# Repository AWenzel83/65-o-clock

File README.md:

# 65-o-clock
6502 based clock heavily inspired by Ben Eaters 6502-Breadboard-Computer (https://eater.net/6502)

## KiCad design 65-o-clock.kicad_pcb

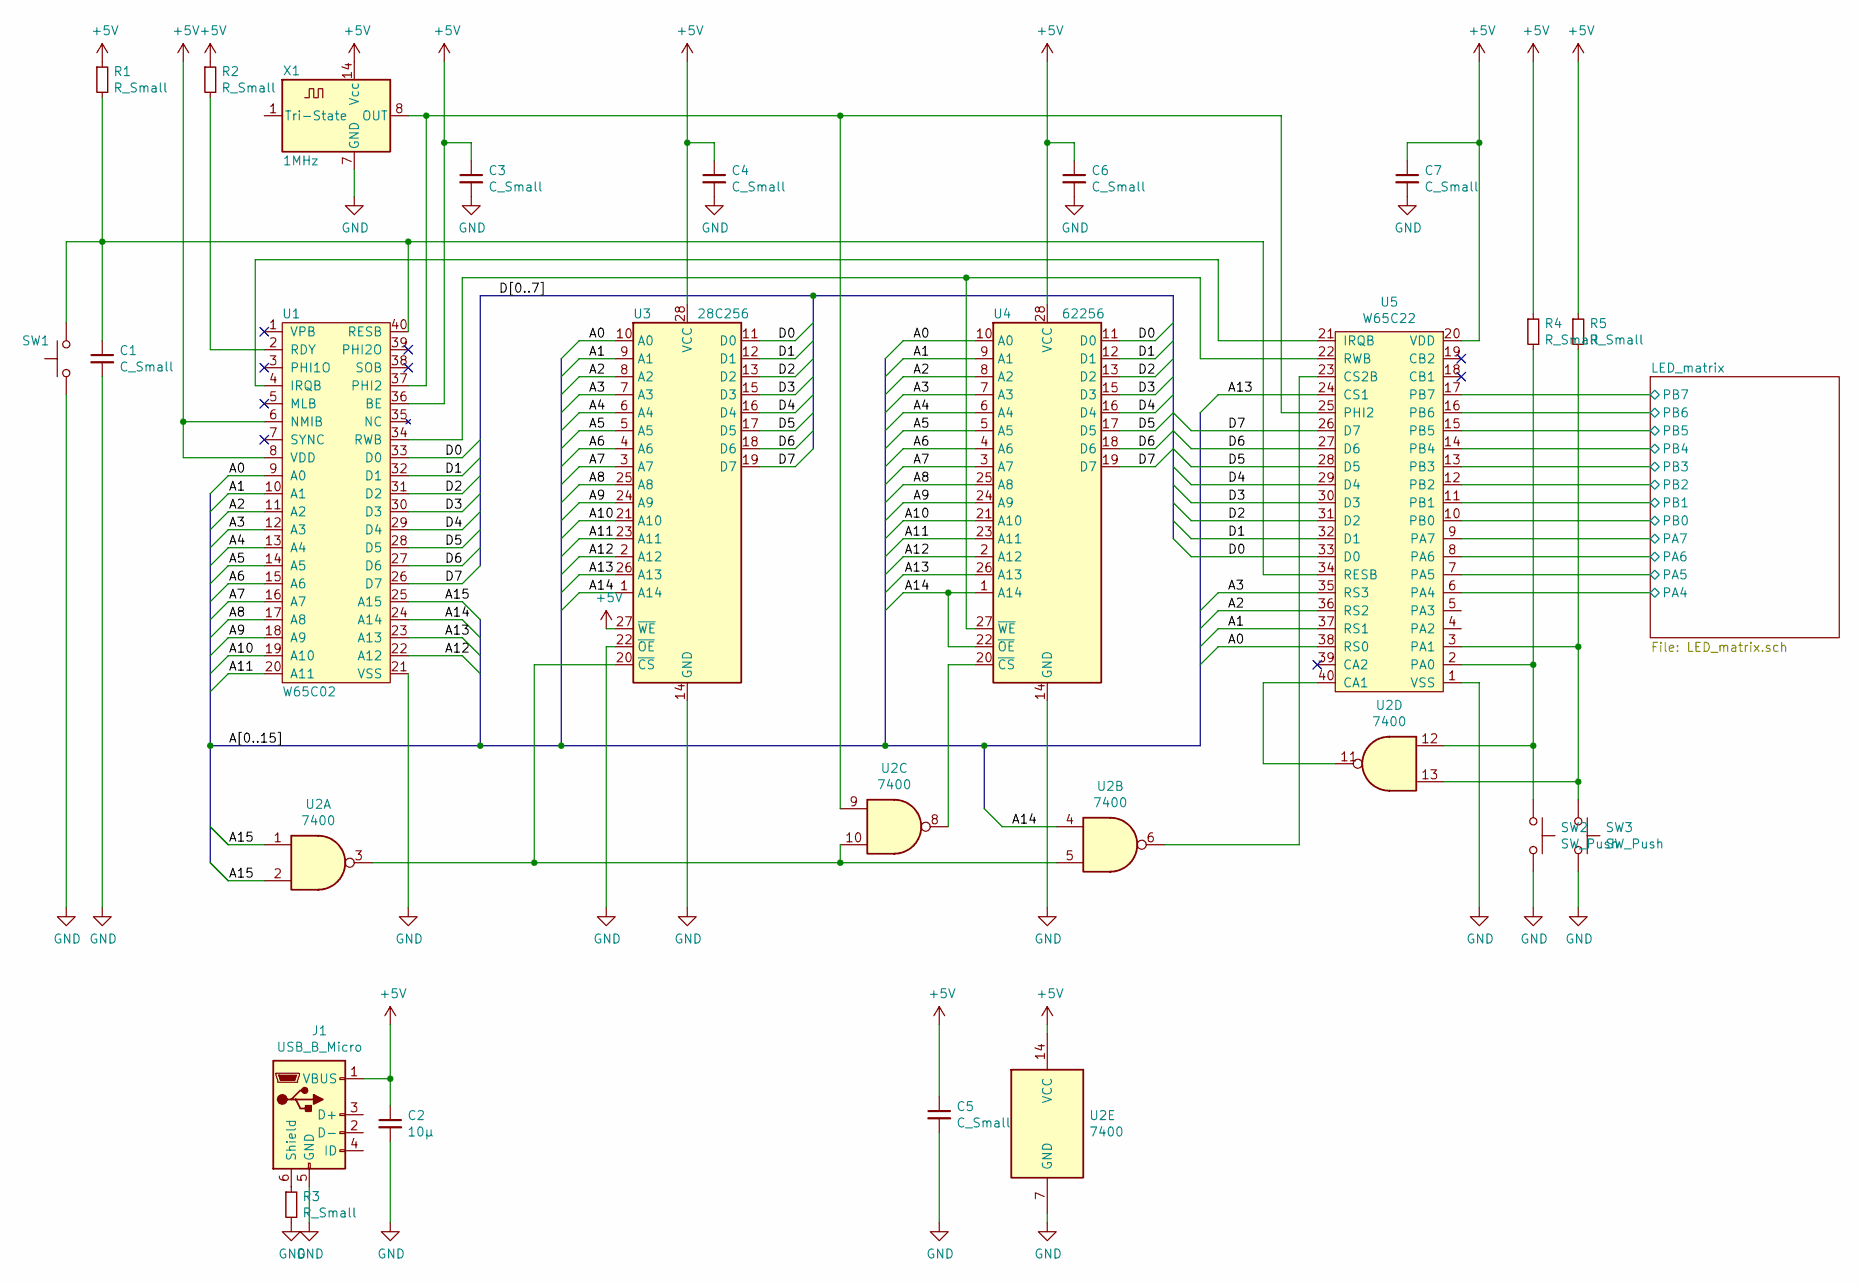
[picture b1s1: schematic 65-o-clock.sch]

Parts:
C1, C3, C4, C5, C6, C7: C_Small; C_0603_1608Metric_Pad1.05x0.95mm_HandSolder
C2: 10µ; C_1206_3216Metric_Pad1.42x1.75mm_HandSolder
J1: USB_B_Micro; USB_Micro-B_Molex-105017-0001
R1, R2, R3, R4, R5: R_Small; R_0603_1608Metric_Pad1.05x0.95mm_HandSolder
SW1, SW2, SW3: SW_Push; SW_Tactile_SPST_Angled_PTS645Vx39-2LFS
U1: W65C02; DIP-40_W15.24mm_Socket_LongPads
U2: 7400; DIP-14_W7.62mm_Socket_LongPads
U3: 28C256; DIP-28_W15.24mm_Socket_LongPads
U4: 62256; DIP-28_W15.24mm_Socket_LongPads
U5: W65C22; DIP-40_W15.24mm_Socket_LongPads
X1: 1MHz; Oscillator_DIP-14

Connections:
+5V: C2.1, C3.1, C4.1, C5.1, C6.1, C7.1, J1.1 (VBUS), R1.1, R2.1, R4.1, R5.1, U1.6 (NMIB), U1.8 (VDD), U1.36 (BE), U2.14 (VCC), U3.27 (~WE), U3.28 (VCC), U4.28 (VCC), U5.20 (VDD), X1.14 (Vcc); also elsewhere on the board
/A0: U1.9 (A0), U3.10 (A0), U4.10 (A0), U5.38 (RS0)
/A1: U1.10 (A1), U3.9 (A1), U4.9 (A1), U5.37 (RS1)
/A2: U1.11 (A2), U3.8 (A2), U4.8 (A2), U5.36 (RS2)
/A3: U1.12 (A3), U3.7 (A3), U4.7 (A3), U5.35 (RS3)
/A4: U1.13 (A4), U3.6 (A4), U4.6 (A4)
/A5: U1.14 (A5), U3.5 (A5), U4.5 (A5)
/A6: U1.15 (A6), U3.4 (A6), U4.4 (A6)
/A7: U1.16 (A7), U3.3 (A7), U4.3 (A7)
/A8: U1.17 (A8), U3.25 (A8), U4.25 (A8)
/A9: U1.18 (A9), U3.24 (A9), U4.24 (A9)
/A10: U1.19 (A10), U3.21 (A10), U4.21 (A10)
/A11: U1.20 (A11), U3.23 (A11), U4.23 (A11)
/A12: U1.22 (A12), U3.2 (A12), U4.2 (A12)
/A13: U1.23 (A13), U3.26 (A13), U4.26 (A13), U5.24 (CS1)
/A14: U1.24 (A14), U2.4, U3.1 (A14), U4.1 (A14), U4.22 (~OE)
/A15: U1.25 (A15), U2.1, U2.2
/D0: U1.33 (D0), U3.11 (D0), U4.11 (D0), U5.33 (D0)
/D1: U1.32 (D1), U3.12 (D1), U4.12 (D1), U5.32 (D1)
/D2: U1.31 (D2), U3.13 (D2), U4.13 (D2), U5.31 (D2)
/D3: U1.30 (D3), U3.15 (D3), U4.15 (D3), U5.30 (D3)
/D4: U1.29 (D4), U3.16 (D4), U4.16 (D4), U5.29 (D4)
/D5: U1.28 (D5), U3.17 (D5), U4.17 (D5), U5.28 (D5)
/D6: U1.27 (D6), U3.18 (D6), U4.18 (D6), U5.27 (D6)
/D7: U1.26 (D7), U3.19 (D7), U4.19 (D7), U5.26 (D7)
/LED_matrix/PA4: U5.6 (PA4); also elsewhere on the board
/LED_matrix/PA5: U5.7 (PA5); also elsewhere on the board
/LED_matrix/PA6: U5.8 (PA6); also elsewhere on the board
/LED_matrix/PA7: U5.9 (PA7); also elsewhere on the board
/LED_matrix/PB0: U5.10 (PB0); also elsewhere on the board
/LED_matrix/PB1: U5.11 (PB1); also elsewhere on the board
/LED_matrix/PB2: U5.12 (PB2); also elsewhere on the board
/LED_matrix/PB3: U5.13 (PB3); also elsewhere on the board
/LED_matrix/PB4: U5.14 (PB4); also elsewhere on the board
/LED_matrix/PB5: U5.15 (PB5); also elsewhere on the board
/LED_matrix/PB6: U5.16 (PB6); also elsewhere on the board
/LED_matrix/PB7: U5.17 (PB7); also elsewhere on the board
GND: C1.2, C2.2, C3.2, C4.2, C5.2, C6.2, C7.2, J1.5 (GND), R3.2, SW1.1, SW2.2, SW3.2, U1.21 (VSS), U2.7 (GND), U3.14 (GND), U3.22 (~OE), U4.14 (GND), U5.1 (VSS), X1.7 (GND); also elsewhere on the board
unnamed: C1.1, R1.2, SW1.2, U1.40 (RESB), U5.34 (RESB)
unnamed: J1.6 (Shield), R3.1
unnamed: R2.2, U1.2 (RDY)
unnamed: R4.2, SW2.1, U2.12, U5.2 (PA0)
unnamed: R5.2, SW3.1, U2.13, U5.3 (PA1)
unnamed: U1.4 (IRQB), U5.21 (IRQB)
unnamed: U1.34 (RWB), U4.27 (~WE), U5.22 (RWB)
unnamed: U1.37 (PHI2), U2.9, U5.25 (PHI2), X1.8 (OUT)
unnamed: U2.6, U5.23 (CS2B)
unnamed: U2.8, U4.20 (~CS)
unnamed: U2.3, U2.5, U2.10, U3.20 (~CS)
unnamed: U2.11, U5.40 (CA1)

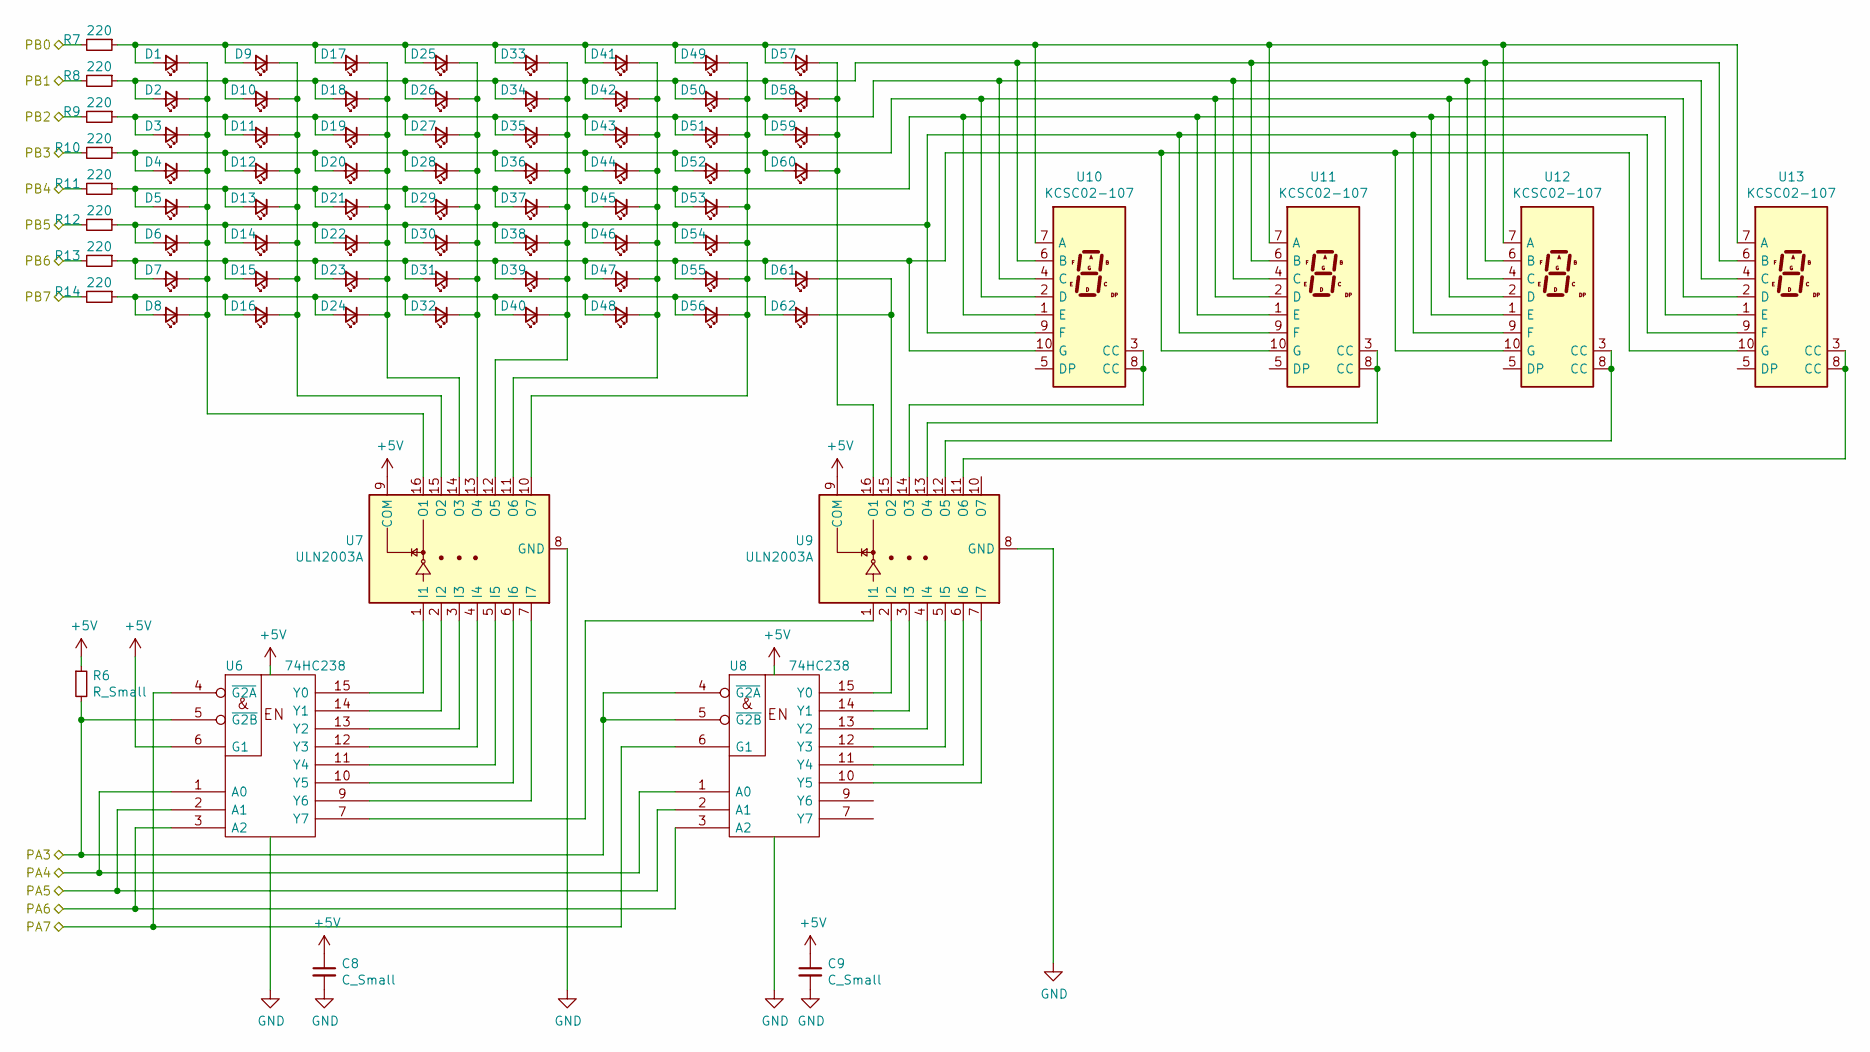
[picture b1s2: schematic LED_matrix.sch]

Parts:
C8, C9: C_Small; C_0603_1608Metric_Pad1.05x0.95mm_HandSolder
D1, D2, D3, D4, D5, D6, D7, D8, D9, D10, D11, D12, D13, D14, D15, D16, D17, D18, D19, D20, D21, D22, D23, D24, D25, D26, D27, D28, D29, D30, D31, D32, D33, D34, D35, D36, D37, D38, D39, D40, D41, D42, D43, D44, D45, D46, D47, D48, D49, D50, D51, D52, D53, D54, D55, D56, D57, D58, D59, D60, D61, D62: LED_Small; LED_D5.0mm
R6: R_Small; R_0603_1608Metric_Pad1.05x0.95mm_HandSolder
R7, R8, R9, R10, R11, R12, R13, R14: 220; R_0603_1608Metric_Pad1.05x0.95mm_HandSolder
U6, U8: 74HC238; DIP-16_W7.62mm_Socket_LongPads
U7, U9: ULN2003A; DIP-16_W7.62mm_Socket_LongPads
U10, U11, U12, U13: KCSC02-107; 7SegmentLED_LTS6760_LTS6780

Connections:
+5V: C8.1, C9.1, R6.1, U6.6 (G1), U6.16 (VCC), U7.9 (COM), U8.16 (VCC), U9.9 (COM); also elsewhere on the board
/LED_matrix/PA3: R6.2, U6.5 (~G2B), U8.4 (~G2A), U8.5 (~G2B)
/LED_matrix/PA4: U6.1 (A0), U8.1 (A0); also elsewhere on the board
/LED_matrix/PA5: U6.2 (A1), U8.2 (A1); also elsewhere on the board
/LED_matrix/PA6: U6.3 (A2), U8.3 (A2); also elsewhere on the board
/LED_matrix/PA7: U6.4 (~G2A), U8.6 (G1); also elsewhere on the board
/LED_matrix/PB0: R7.2; also elsewhere on the board
/LED_matrix/PB1: R8.2; also elsewhere on the board
/LED_matrix/PB2: R9.2; also elsewhere on the board
/LED_matrix/PB3: R10.2; also elsewhere on the board
/LED_matrix/PB4: R11.2; also elsewhere on the board
/LED_matrix/PB5: R12.2; also elsewhere on the board
/LED_matrix/PB6: R13.2; also elsewhere on the board
/LED_matrix/PB7: R14.2; also elsewhere on the board
GND: C8.2, C9.2, U6.8 (GND), U7.8 (GND), U8.8 (GND), U9.8 (GND); also elsewhere on the board
unnamed: D1.1 (K), D2.1 (K), D3.1 (K), D4.1 (K), D5.1 (K), D6.1 (K), D7.1 (K), D8.1 (K), U7.16 (O1)
unnamed: D1.2 (A), D9.2 (A), D17.2 (A), D25.2 (A), D33.2 (A), D41.2 (A), D49.2 (A), D57.2 (A), R7.1, U10.7 (A), U11.7 (A), U12.7 (A), U13.7 (A)
unnamed: D9.1 (K), D10.1 (K), D11.1 (K), D12.1 (K), D13.1 (K), D14.1 (K), D15.1 (K), D16.1 (K), U7.15 (O2)
unnamed: D2.2 (A), D10.2 (A), D18.2 (A), D26.2 (A), D34.2 (A), D42.2 (A), D50.2 (A), D58.2 (A), R8.1, U10.6 (B), U11.6 (B), U12.6 (B), U13.6 (B)
unnamed: D3.2 (A), D11.2 (A), D19.2 (A), D27.2 (A), D35.2 (A), D43.2 (A), D51.2 (A), D59.2 (A), R9.1, U10.4 (C), U11.4 (C), U12.4 (C), U13.4 (C)
unnamed: D4.2 (A), D12.2 (A), D20.2 (A), D28.2 (A), D36.2 (A), D44.2 (A), D52.2 (A), D60.2 (A), R10.1, U10.2 (D), U11.2 (D), U12.2 (D), U13.2 (D)
unnamed: D5.2 (A), D13.2 (A), D21.2 (A), D29.2 (A), D37.2 (A), D45.2 (A), D53.2 (A), R11.1, U10.1 (E), U11.1 (E), U12.1 (E), U13.1 (E)
unnamed: D6.2 (A), D14.2 (A), D22.2 (A), D30.2 (A), D38.2 (A), D46.2 (A), D54.2 (A), R12.1, U10.9 (F), U11.9 (F), U12.9 (F), U13.9 (F)
unnamed: D7.2 (A), D15.2 (A), D23.2 (A), D31.2 (A), D39.2 (A), D47.2 (A), D55.2 (A), D61.2 (A), R13.1, U10.10 (G), U11.10 (G), U12.10 (G), U13.10 (G)
unnamed: D8.2 (A), D16.2 (A), D24.2 (A), D32.2 (A), D40.2 (A), D48.2 (A), D56.2 (A), D62.2 (A), R14.1
unnamed: D17.1 (K), D18.1 (K), D19.1 (K), D20.1 (K), D21.1 (K), D22.1 (K), D23.1 (K), D24.1 (K), U7.14 (O3)
unnamed: D25.1 (K), D26.1 (K), D27.1 (K), D28.1 (K), D29.1 (K), D30.1 (K), D31.1 (K), D32.1 (K), U7.13 (O4)
unnamed: D33.1 (K), D34.1 (K), D35.1 (K), D36.1 (K), D37.1 (K), D38.1 (K), D39.1 (K), D40.1 (K), U7.12 (O5)
unnamed: D41.1 (K), D42.1 (K), D43.1 (K), D44.1 (K), D45.1 (K), D46.1 (K), D47.1 (K), D48.1 (K), U7.11 (O6)
unnamed: D49.1 (K), D50.1 (K), D51.1 (K), D52.1 (K), D53.1 (K), D54.1 (K), D55.1 (K), D56.1 (K), U7.10 (O7)
unnamed: D57.1 (K), D58.1 (K), D59.1 (K), D60.1 (K), U9.16 (O1)
unnamed: D61.1 (K), D62.1 (K), U9.15 (O2)
unnamed: U6.7 (Y7), U9.1 (I1)
unnamed: U6.9 (Y6), U7.7 (I7)
unnamed: U6.10 (Y5), U7.6 (I6)
unnamed: U6.11 (Y4), U7.5 (I5)
unnamed: U6.12 (Y3), U7.4 (I4)
unnamed: U6.13 (Y2), U7.3 (I3)
unnamed: U6.14 (Y1), U7.2 (I2)
unnamed: U6.15 (Y0), U7.1 (I1)
unnamed: U8.10 (Y5), U9.7 (I7)
unnamed: U8.11 (Y4), U9.6 (I6)
unnamed: U8.12 (Y3), U9.5 (I5)
unnamed: U8.13 (Y2), U9.4 (I4)
unnamed: U8.14 (Y1), U9.3 (I3)
unnamed: U8.15 (Y0), U9.2 (I2)
unnamed: U9.14 (O3), U10.3 (CC), U10.8 (CC)
unnamed: U9.13 (O4), U11.3 (CC), U11.8 (CC)
unnamed: U9.12 (O5), U12.3 (CC), U12.8 (CC)
unnamed: U9.11 (O6), U13.3 (CC), U13.8 (CC)

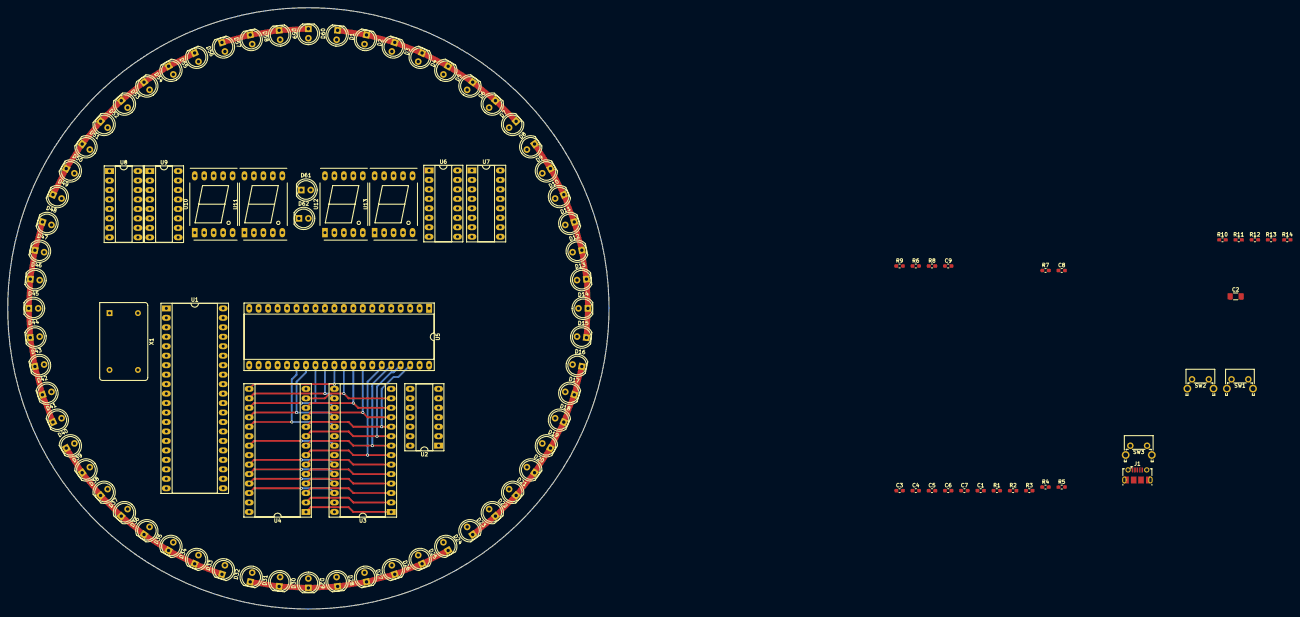
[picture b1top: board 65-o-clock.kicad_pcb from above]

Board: 2 copper layers, 161.3 x 161.3 mm, 103 parts (0 on the bottom side), 86 nets.

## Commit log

2020-10-07 First revision of the Schematic
2020-10-09 Diodes placed, layout started
